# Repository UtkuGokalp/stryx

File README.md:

# Stryx

Stryx is a 3D printable wheeled robot designed as a platform for embedded software development. It has:
 - A power system that handles multiple power rails
 - An STM32 MCU (Nucleo L432KC) for controlling motors, sensors and potential future hardwares
 - An ultrasonic sensor for detecting obstacles
 - USB Connectivity
 - A modular platform that allows secure mounting
 - Various custom mounts

# Features
 - 3D printable parts (without supports)
 - Rear wheel drive via DC motors
 - Power system for managing different power rails
 - STM32 Nucleo L432KC MCU for real time control
 - Basic obstacle avoidance
 - DSP for removing sensor noises
 - Designed to be built on a mid-size breadboard for ease of prototyping and compactness
 - USB connectivity for universal communication (to be integrated better)

# Pictures
Below are the front, top and bottom views of Stryx.

# Videos
  - A video of Stryx moving can be viewed [here](https://youtube.com/shorts/t5ViIWTwRgw?feature=share).
  - A video of Stryx detection through the ultrasonic sensor can be viewed [here](https://youtu.be/18g5bbReIh8).
 - Stryx being controlled by a custom controller and avoiding collisions can be viewed [here](https://youtube.com/shorts/JMSHhV6Dkls?si=vsp8z5HZcUrGIarE).

# Roadmap
Current plans to improve this project are in the following order:
 - PCB design
 - Better joystick controls
 - Better sensing of environment with either
   1. More sensors
   2. Servos that control the orientation of sensors
   3. Or sensors that use different technologies such as IR or LiDAR

# Parts List
|Name|Amount|
|-----|-----|
|Mid-size breadboard|1|
|STM32 Nucleo L432KC Dev Board|1|
|USB Micro-B breakout board|1|
|TB6612FNG Module|1|
|12V 250RPM DC Motors|2|
|Omnidirectional Wheels|2|
|LM317T Voltage regulator |1|
|1N4001|3|
|1N5822|1|
|0.1uF ceramic capacitor|2|
|1uF polarized capacitor|1|
|10uF polarized capacitor|1|
|470uF polarized capacitor|2|
|240Ω resistor|1|
|1kΩ resistor|2|
|3.8kΩ resistor|1|
|Neopixel LED Module|1|
|HC-SR04 ultrasonic sensor|1|
|3S 20A BMS|1|
|3200mAh Li-ion batteries|3|
|3S Li-ion battery holder|1|
|Switch (SPDT)|1|
|Screw Terminals|3|
|Rubber Wheels with D-Shaft connections|2|
|M3 screws, nuts, spacers and cables|various amounts|

# Schematic

Schematic is available in `kicad_files/` folder along with a PDF for quick viewing of the schematic.

Note: PDF may be outdated. KiCad project is the most up to date schematic.

# 3D Models

All 3D model files are in `3D_models/` folder along with printing instructions.

# How to build
## Mechanical
All parts are designed to align with the chassis mounting holes. Parts can be mounted wherever suitable, but keep in mind:
 - Wire lengths
 - Weight distribution and center of gravity
 - Accessibility

## Electronics
Components can be wired up according to the schematic in `kicad_files/`.

## Software
 1. Create a new STM32CubeIDE project using the `.ioc` file.
 2. Build the project.
 3. Connect the development board to the computer.
 4. Upload the firmware.

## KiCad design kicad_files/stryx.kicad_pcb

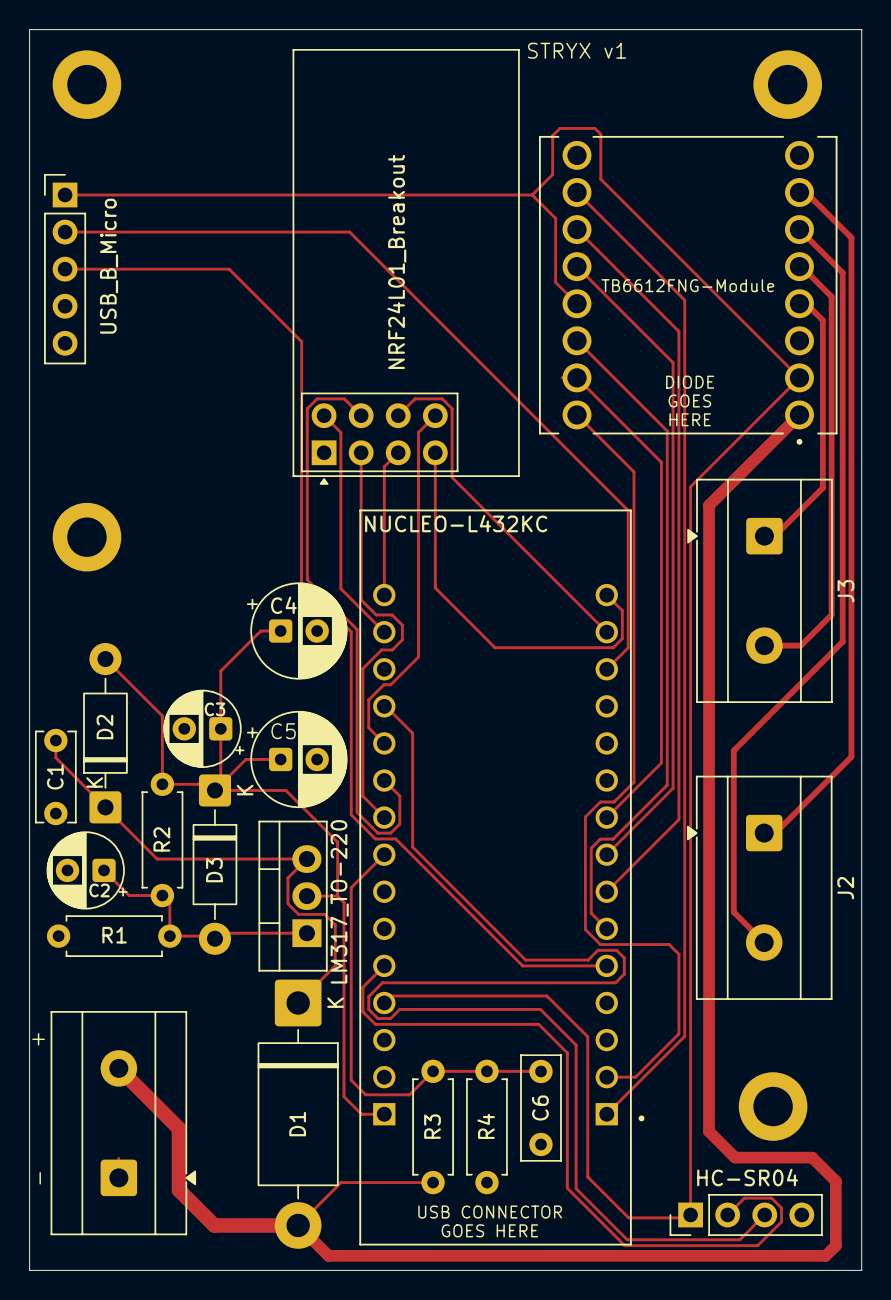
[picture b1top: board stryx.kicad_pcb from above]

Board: 2 copper layers, 57.0 x 85.0 mm, 22 parts (0 on the bottom side), 28 nets.

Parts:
C1: 0.1uF; C_Disc_D6.0mm_W2.5mm_P5.00mm
C2: 10uF 50V; CP_Radial_D5.0mm_P2.50mm
C3: 1uF 50V; CP_Radial_D5.0mm_P2.50mm
C4, C5: 470uF 10V; CP_Radial_D6.3mm_P2.50mm
C6: 0.1uF; C_Rect_L7.0mm_W2.5mm_P5.00mm
D1: 1N5822; D_DO-201AD_P15.24mm_Horizontal
D2, D3: 1N4001; D_DO-41_SOD81_P10.16mm_Horizontal
J1: Screw_Terminal_Power; TerminalBlock_MetzConnect_Type171_RT13702HBWC_1x02_P7.50mm_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
J2: Screw_Terminal_M2; TerminalBlock_MetzConnect_Type171_RT13702HBWC_1x02_P7.50mm_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
J3: Screw_Terminal_M1; TerminalBlock_MetzConnect_Type171_RT13702HBWC_1x02_P7.50mm_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
J4: USB_B_Micro; PinHeader_1x05_P2.54mm_Vertical
R1, R4: 1k; R_Axial_DIN0207_L6.3mm_D2.5mm_P7.62mm_Horizontal
R2: 240R; R_Axial_DIN0207_L6.3mm_D2.5mm_P7.62mm_Horizontal
R3: 3.8k; R_Axial_DIN0207_L6.3mm_D2.5mm_P7.62mm_Horizontal
U1: LM317_TO-220; TO-220-3_Vertical
U2: NUCLEO-L432KC; MODULE_NUCLEO-L432KC
U3: HC-SR04; PinHeader_1x04_P2.54mm_Vertical
U4: TB6612FNG-Module; MODULE_ROB-14450
U5: NRF24L01_Breakout; nRF24L01_Breakout

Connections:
6.8V: C3.1, C4.1, C5.1, D2.2 (A), D3.1 (K), R2.1, U1.2 (VO), U2.CN4_1 (VIN)
+3V3: U2.CN4_14 (+3V3), U5.2 (VCC)
+5V: J4.1 (VBUS), U2.CN4_4 (+5V), U3.1 (VCC), U4.2 (VCC), U4.13 (STBY)
Dir1_M1: U2.CN3_6 (PB0), U4.14 (AI1)
Dir1_M2: U2.CN3_8 (PB6), U4.12 (BI1)
Dir2_M1: U2.CN3_9 (PB1), U4.15 (AI2)
Dir2_M2: U2.CN3_7 (PB7), U4.11 (BI2)
GNDREF: C1.1, C2.2, C3.2, C4.2, C5.2, C6.1, J1.1, J4.5 (GND), R1.2, R4.2, U2.CN3_4 (GND_CN3), U2.CN4_2 (GND_CN4), U3.4 (GND), U4.3 (GND), U4.8 (GND), U4.9 (GND), U5.1 (GND)
unnamed: C1.2, D1.1 (K), D2.1 (K), U1.3 (VI)
unnamed: C2.1, D3.2 (A), R1.1, R2.2, U1.1 (ADJ)
unnamed: J2.1, U4.7 (B01)
unnamed: J2.2, U4.6 (B02)
unnamed: J3.1, U4.4 (A01)
unnamed: J3.2, U4.5 (A02)
PWM_M1: U2.CN3_2 (PA10), U4.16 (PWMA)
PWM_M2: U2.CN3_1 (PA9), U4.10 (PWMB)
Sonar_ECHO: U2.CN4_12 (PA0), U3.3 (ECHO)
Sonar_TRIG: U2.CN4_5 (PA2), U3.2 (TRIG)
USB_D+: J4.3 (D+), U2.CN3_5 (PA12)
USB_D-: J4.2 (D-), U2.CN3_13 (PA11)
Vbat: D1.2 (A), J1.2, R3.1, U4.1 (VM)
Vbat_Sense: C6.2, R3.2, R4.1, U2.CN4_8 (PA5)
Wireless_CE: U2.CN4_9 (PA4), U5.3 (CE)
Wireless_CSNB: U2.CN4_10 (PA3), U5.4 (~CSN)
Wireless_IRQ: U2.CN4_11 (PA1), U5.8 (IRQ)
Wireless_MISO: U2.CN3_15 (PB4), U5.7 (MISO)
Wireless_MOSI: U2.CN3_14 (PB5), U5.6 (MOSI)
Wireless_SCK: U2.CN4_15 (PB3), U5.5 (SCK)

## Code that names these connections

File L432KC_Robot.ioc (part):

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Mcu.Name=STM32L432K(B-C)Ux
Mcu.Package=UFQFPN32
Mcu.UserName=STM32L432KCUx
PA0.GPIOParameters=GPIO_Label
PA0.GPIO_Label=HCSR04_Echo
PA0.Signal=S_TIM2_CH1
PA1.GPIOParameters=GPIO_Label
PA1.GPIO_Label=nRF24L01_IRQ
PA1.Signal=GPIO_Input
PA10.GPIOParameters=GPIO_Label
PA10.GPIO_Label=MotorA_PWM
PA10.Signal=S_TIM1_CH3
PA11.Mode=Device
PA11.Signal=USB_DM
PA12.Mode=Device
PA12.Signal=USB_DP
PA13\ (JTMS-SWDIO).Mode=Serial_Wire
PA13\ (JTMS-SWDIO).Signal=SYS_JTMS-SWDIO
PA14\ (JTCK-SWCLK).Mode=Serial_Wire
PA14\ (JTCK-SWCLK).Signal=SYS_JTCK-SWCLK
PA2.GPIOParameters=GPIO_Label
PA2.GPIO_Label=HCSR04_Trig
PA2.Signal=S_TIM15_CH1
PA3.GPIOParameters=GPIO_Label
PA3.GPIO_Label=nRF24L01_CSN
PA3.Signal=GPIO_Output
PA4.GPIOParameters=GPIO_Label
PA4.GPIO_Label=nRF24L01_CE
PA4.Signal=GPIO_Output
PA5.GPIOParameters=GPIO_Label
PA5.GPIO_Label=BAT_SENSE
PA5.Signal=ADCx_IN10
PA8.GPIOParameters=GPIO_Label
PA8.GPIO_Label=NeoPixel_PWM
PA8.Signal=S_TIM1_CH1
PA9.GPIOParameters=GPIO_Label
PA9.GPIO_Label=MotorB_PWM
PA9.Signal=S_TIM1_CH2
PB0.GPIOParameters=GPIO_Label
PB0.GPIO_Label=MotorA_In1
PB0.Signal=GPIO_Output
PB1.GPIOParameters=GPIO_Label
PB1.GPIO_Label=MotorA_In2
PB1.Signal=GPIO_Output
PB3\ (JTDO-TRACESWO).Mode=Full_Duplex_Master
PB3\ (JTDO-TRACESWO).Signal=SPI3_SCK
PB4\ (NJTRST).Mode=Full_Duplex_Master
PB4\ (NJTRST).Signal=SPI3_MISO
PB5.Mode=Full_Duplex_Master
PB5.Signal=SPI3_MOSI
PB6.GPIOParameters=GPIO_Label
PB6.GPIO_Label=MotorB_In1
PB6.Signal=GPIO_Output
PB7.GPIOParameters=GPIO_Label
PB7.GPIO_Label=MotorB_In2
PB7.Signal=GPIO_Output
RCC.HSE_VALUE=8000000
RCC.SYSCLKFreq_VALUE=32000000
RCC.SYSCLKSource=RCC_SYSCLKSOURCE_PLLCLK
board=NUCLEO-L432KC

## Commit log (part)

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2026-05-03 Added MIT License
2026-05-03 Added the schematic as a pdf file
2026-05-03 Updated 3D printing instructions
2026-05-03 Updated schematic and deleted auto-generated backups. A future commit will disable tracking of backups
2026-05-03 Updated .gitignore to not track kicad backups and lock files
2026-05-03 Add README
2026-05-05 Added USB functionality for future use while the pins are still free.
2026-05-05 Add USB connectivity information to README
2026-05-05 Updated schematic to include USB connectivity
2026-05-05 Add USB Micro-B breakout board to components list
2026-05-07 Analyzed the sensor data, designed a proper filter, removed unnecesary timer usage and fixed issues with reading sensor data
2026-05-07 Update README with improvements and new features
    Removed redundant phrasing and added DSP for noise removal.
2026-05-07 Update README with video links for Stryx
    Added links to videos demonstrating Stryx's movement and ultrasonic detection.
2026-05-07 Added photos of Stryx
2026-05-07 Refactor pictures and videos sections in README
    Updated the README to improve the organization of pictures and videos sections.
2026-05-07 Update roadmap
2026-06-13 fixed interrupt mess by using HAL interrupt callback system
2026-06-14 Generated STM32 SPI HAL for implementing nRF24L01 driver
2026-06-14 Fixed SPI configuration on CubeMX
2026-06-15 Implemented the SPI communication and reading register for nRF24L01
2026-06-17 Completed the nRF24L01 driver for receiving signals
2026-06-22 Fixed a bug with the TB6612FNG driver code and started experimentations for joystick controls
2026-06-22 Redirected printf to USB and fixed function calling bug.
2026-06-24 Added the design file for nRF24L01 mount
2026-06-24 Updated schematic
